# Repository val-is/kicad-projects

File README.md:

# kicad-projects
monorepo for pcb design + electronic projects

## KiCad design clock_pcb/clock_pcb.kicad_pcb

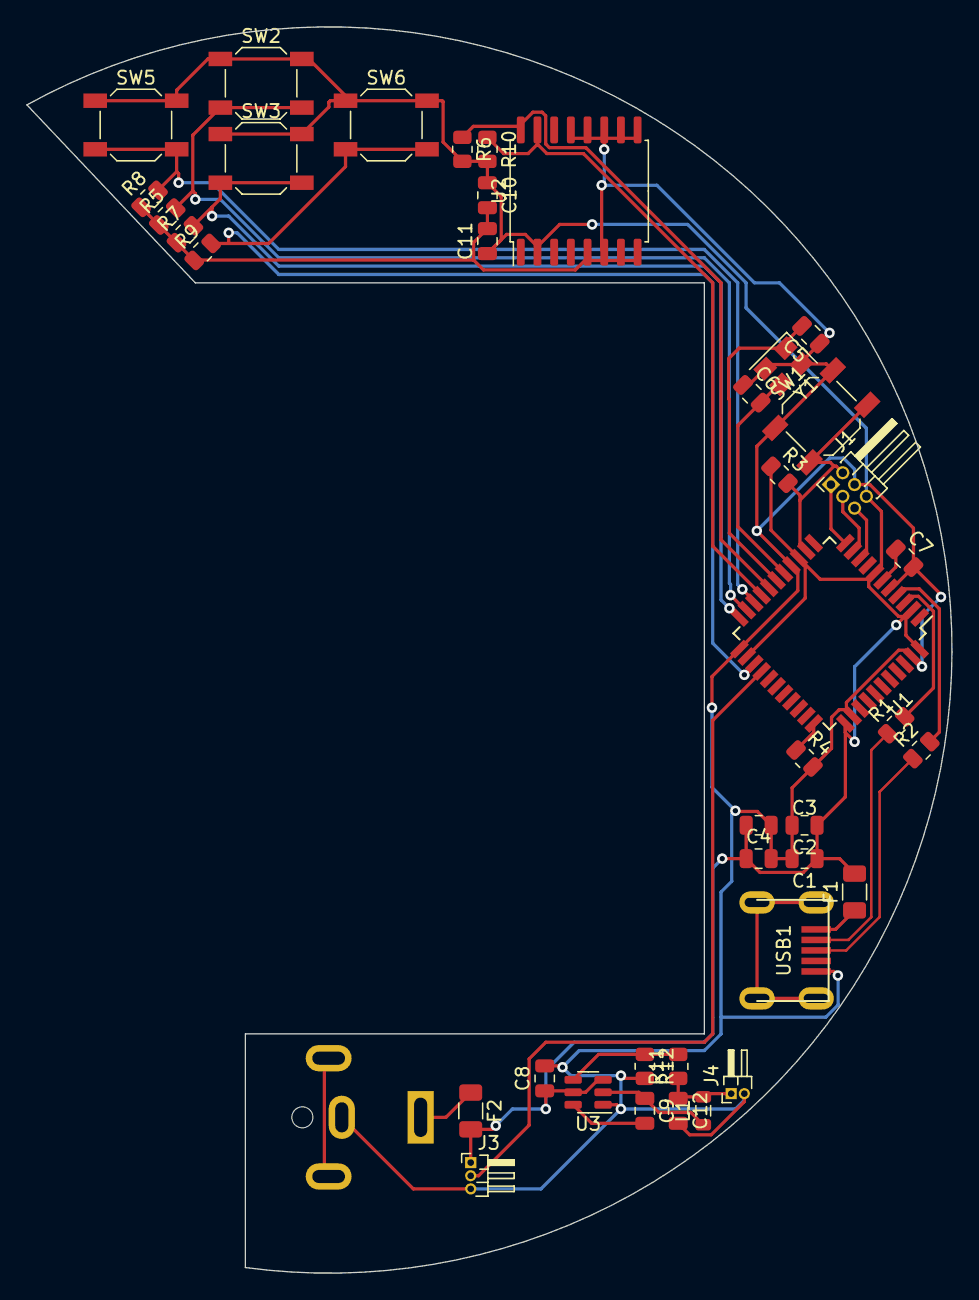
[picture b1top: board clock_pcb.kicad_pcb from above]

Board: 2 copper layers, 70.4 x 94.8 mm, 41 parts (1 on the bottom side), 27 nets.

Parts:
C1, C2, C3, C11: 0.1uF; C_0805_2012Metric
C4, C8, C10: 10uF; C_0805_2012Metric
C5, C6: 22pF; C_0805_2012Metric
C7: 1uF; C_0805_2012Metric
C9: 100nF; C_0805_2012Metric
C12: 22uF; C_0805_2012Metric
F1, F2: 500mA; Fuse_1206_3216Metric
J1: Conn_02x03_Counter_Clockwise; PinHeader_2x03_P1.27mm_Horizontal
J2: Barrel_Jack_MountingPin; BarrelJack_CUI_PJ-063AH_Horizontal
J3: Conn_01x03; PinHeader_1x03_P1.00mm_Horizontal
J4: Conn_01x02; PinHeader_1x02_P1.00mm_Horizontal
L1: 1.5uH; L_0805_2012Metric
R1, R2: 22; R_0805_2012Metric
R3, R4, R5, R6, R7, R8, R9, R10, R12: 10k; R_0805_2012Metric
R11: 5.76k; R_0805_2012Metric
SW1, SW2, SW3, SW5, SW6: SW_Push; SW_SPST_SKQG_WithStem
U1: ATmega32U4-A; TQFP-44_10x10mm_P0.8mm
U2: DS3231M; SOIC-16W_7.5x10.3mm_P1.27mm
U3: TPS562200; SOT-23-6
USB1: Molex-0548190589
Y1: 16MHz; Crystal_SMD_3225-4Pin_3.2x2.5mm

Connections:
+1V5: C12.1, J4.1, L1.2, R11.1
+5V: C1.1, C2.1, C3.1, C4.1, C8.1, C10.1, C11.1, F1.2, F2.2, J1.6, J3.1, R3.1, R6.2, R10.2, SW2.1, SW3.1, SW5.1, SW6.1, U1.2 (UVCC), U1.7 (VBUS), U1.14 (VCC), U1.24 (AVCC), U1.34 (VCC), U1.44 (AVCC), U2.2 (VCC), U3.3 (VIN), U3.5 (EN)
D+: R2.1, USB1.3 (D+)
D-: R1.1, USB1.4 (D-)
DP_DOWN: R7.2, SW3.2, U1.22 (PD5)
DP_LEFT: R8.2, SW5.2, U1.20 (PD2)
DP_RIGHT: R9.2, SW6.2, U1.25 (PD4)
DP_UP: R5.2, SW2.2, U1.21 (PD3)
GND: C1.2, C2.2, C3.2, C4.2, C5.1, C6.1, C7.2, C8.2, C10.2, C11.2, C12.2, J1.4, J2.2, J3.3, J4.2, R4.2, R5.1, R7.1, R8.1, R9.1, R12.2, SW1.1, U1.5 (UGND), U1.15 (GND), U1.23 (GND), U1.35 (GND), U1.43 (GND), U2.5 (GND), U2.6 (GND), U2.7 (GND), U2.8 (GND), U2.9 (GND), U2.10 (GND), U2.11 (GND), U2.12 (GND), U2.13 (GND), U3.1 (GND), USB1.1 (GND), Y1.2, Y1.4
LED: J3.2, U1.26 (PD6)
MISO: J1.1, U1.11 (PB3)
MOSI: J1.3, U1.10 (PB2)
unnamed: F2.1, J2.1
unnamed: R2.2, U1.4 (D+)
unnamed: R1.2, U1.3 (D-)
unnamed: C7.1, U1.6 (UCAP)
unnamed: C5.2, U1.17 (XTAL1), Y1.1
unnamed: C6.2, U1.16 (XTAL2), Y1.3
unnamed: R4.1, U1.33 (~HWB/PE2)
unnamed: C9.1, L1.1, U3.2 (SW)
unnamed: C9.2, U3.6 (VBST)
unnamed: R11.2, R12.1, U3.4 (VFB)
RESET: J1.2, R3.2, SW1.2, U1.13 (~RESET)
RTC_SCL: R6.1, U1.18 (PD0), U2.16 (SCL)
RTC_SDA: R10.1, U1.19 (PD1), U2.15 (SDA)
SCLK: J1.5, U1.9 (PB1)
VCC: F1.1, USB1.5 (VBUS)

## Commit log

2023-08-16 add common component library
2023-08-16 add first iteration of clock pcb
